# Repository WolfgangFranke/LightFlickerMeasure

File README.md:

# Light Flicker Measure
## Measures flickering lights, like PWM driven LED-systems, using Arduino.

An old Light Bulb sends 80% constant light and a 20% sine waveform as 100 Hz noise ontop, so no flicker is recognized.

This LED Streetlamp sends a permanent PWM of 264 Hz frequency instead of a steady light! Going for a walk at night, this lamp is really annoying.

Philips Hue Being ceiling light and also the Philips Hue Light Strip+, as well as my Philips Hue RGB light bulbs, run at 1 kHz PWM. That still flickers irritatingly in your eyes when looking around in your appartment. I'm surprised seeing that the Hue Being let's overshoot the light at the begin of a PWM=high, but it may be seen due to the two LEDs providing the CCT.

Talking about LED strips, the Paulmann SimpLED-Strip Set (789.56) dims in the PWM frequency range of 2,5 to 4 kHz. Covered by an opaque plastic housing, this could be considered it as less to no flicker. But if you install the strip in direkt sight, a strong flicker will be recognized when moving head or eyes.

Totally smooth light sent by a Philips Filament Bulb (not dimmable), I really enjoy it.

And how about an old-fashioned Neon Lamp, where we all know it does not give a good light? Yep, it does not give a good light!

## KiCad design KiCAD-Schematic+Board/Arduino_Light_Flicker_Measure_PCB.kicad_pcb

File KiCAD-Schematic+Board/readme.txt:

This folder contains the schematic and board layout in KiCAD format.

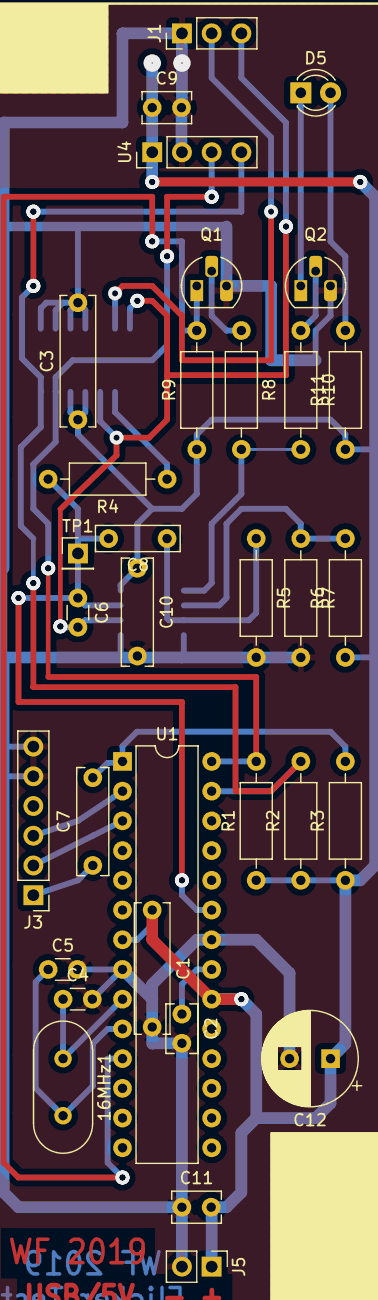
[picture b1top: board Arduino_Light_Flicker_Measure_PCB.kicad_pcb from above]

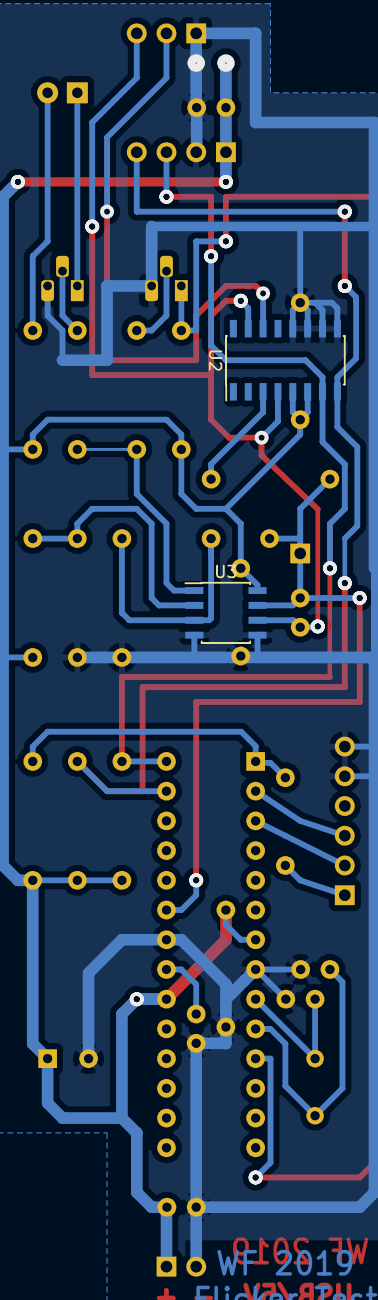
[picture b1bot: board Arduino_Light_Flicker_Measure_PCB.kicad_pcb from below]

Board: 2 copper layers, 35 parts (2 on the bottom side), 23 nets.

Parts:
16MHz1: Q; Crystal_HC49-U_Vertical
C1, C3: 100n; C_Rect_L11.0mm_W2.8mm_P10.00mm_MKT
C2, C9, C11: 100n; C_Rect_L4.0mm_W2.5mm_P2.50mm
C4, C5: 22p; C_Disc_D3.0mm_W1.6mm_P2.50mm
C6: 12p; C_Disc_D3.0mm_W1.6mm_P2.50mm
C7, C10: 100n; C_Rect_L9.0mm_W2.5mm_P7.50mm_MKT
C8: 100n; C_Rect_L7.0mm_W2.0mm_P5.00mm
C12: 1000µ; CP_Radial_D8.0mm_P3.50mm
D5: LED; LED_D3.0mm
J1: Ds; PinHeader_1x03_P2.54mm_Vertical
J3: FTDI; PinHeader_1x06_P2.54mm_Vertical
J5: PWR(5V); PinHeader_1x02_P2.54mm_Vertical
Q1, Q2: BC547; TO-92_HandSolder
R1, R2, R3, R4: 10k; R_Axial_DIN0207_L6.3mm_D2.5mm_P10.16mm_Horizontal
R5: 1M; R_Axial_DIN0207_L6.3mm_D2.5mm_P10.16mm_Horizontal
R6: 120k; R_Axial_DIN0207_L6.3mm_D2.5mm_P10.16mm_Horizontal
R7, R9, R11: 1,5k; R_Axial_DIN0207_L6.3mm_D2.5mm_P10.16mm_Horizontal
R8: 1k; R_Axial_DIN0207_L6.3mm_D2.5mm_P10.16mm_Horizontal
R10: 100k; R_Axial_DIN0207_L6.3mm_D2.5mm_P10.16mm_Horizontal
TP1: TestPoint; PinHeader_1x01_P2.54mm_Vertical
U1: ATmega328P-PU; DIP-28_W7.62mm
U2: AD5242; SOIC-16_3.9x9.9mm_P1.27mm
U3: AD823A; SOIC-8_3.9x4.9mm_P1.27mm
U4: Display; PinHeader_1x04_P2.54mm_Vertical

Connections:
+5V: C1.1, C3.1, C9.1, C10.1, C11.2, C12.1, J5.1, R1.1, R2.1, R3.1, R6.1, R9.1, R11.1, U1.7, U1.20, U2.5, U2.6, U3.8, U4.1
/ADC0: C6.1, C8.2, R4.2, TP1.1, U1.23, U3.7
/RST: C7.1, J3.1
/RX: J3.3, U1.2
/SCL: R1.2, U1.28, U2.7, U4.3
/SDA: R2.2, U1.27, U2.8, U4.4
/TMR1-T1Clock: Q1.1, R9.2, U1.11
/TX: J3.2, U1.3
GNDD: C1.2, C2.2, C3.2, C4.2, C5.2, C9.2, C10.2, C11.1, C12.2, J1.1, J3.5, J3.6, J5.2, Q1.3, Q2.3, R5.2, R7.2, U1.8, U1.22, U2.9, U2.10, U2.11, U2.12, U3.4, U3.5, U4.2
unnamed: 16MHz1.1, C4.1, U1.9
unnamed: 16MHz1.2, C5.1, U1.10
unnamed: C2.1, U1.21
unnamed: C6.2, J1.3, U2.4, U2.15, U3.6
unnamed: C7.2, R3.2, U1.1
unnamed: C8.1, R5.1, U3.3
unnamed: D5.1, Q2.1
unnamed: D5.2, R11.2
unnamed: J1.2, U2.14
unnamed: Q1.2, R8.1
unnamed: Q2.2, R10.1
unnamed: R4.1, U2.3
unnamed: R6.2, R7.1, U3.2
unnamed: R8.2, R10.2, U3.1

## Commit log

2019-04-15 Rename PWM_Flicker_LED+Eye_Mathmatics_DE.txt to PWM_Flicker_LED_+_Eye_Mathmatics_DE.txt
2019-04-15 Rename PWM_Flicker_LED_+_Eye_Mathmatics_DE.txt to Flicker_PWM+Eye_Math_DE.txt
2019-04-15 Rename PWM_Flicker_LED+Eye_Mathmatics_ENGL.txt to Flicker_PWM+Eye_Math_EN
2019-04-15 Rename Flicker_PWM+Eye_Math_EN to Flicker_PWM+Eye_Math_EN.txt
2020-05-23 Create LICENSE
